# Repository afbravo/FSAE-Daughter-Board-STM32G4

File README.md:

# FSAE Daughter Board STM32G4
 Daughter Board KiCad Project for the NYU FSAE with a STM32G4 MCU.

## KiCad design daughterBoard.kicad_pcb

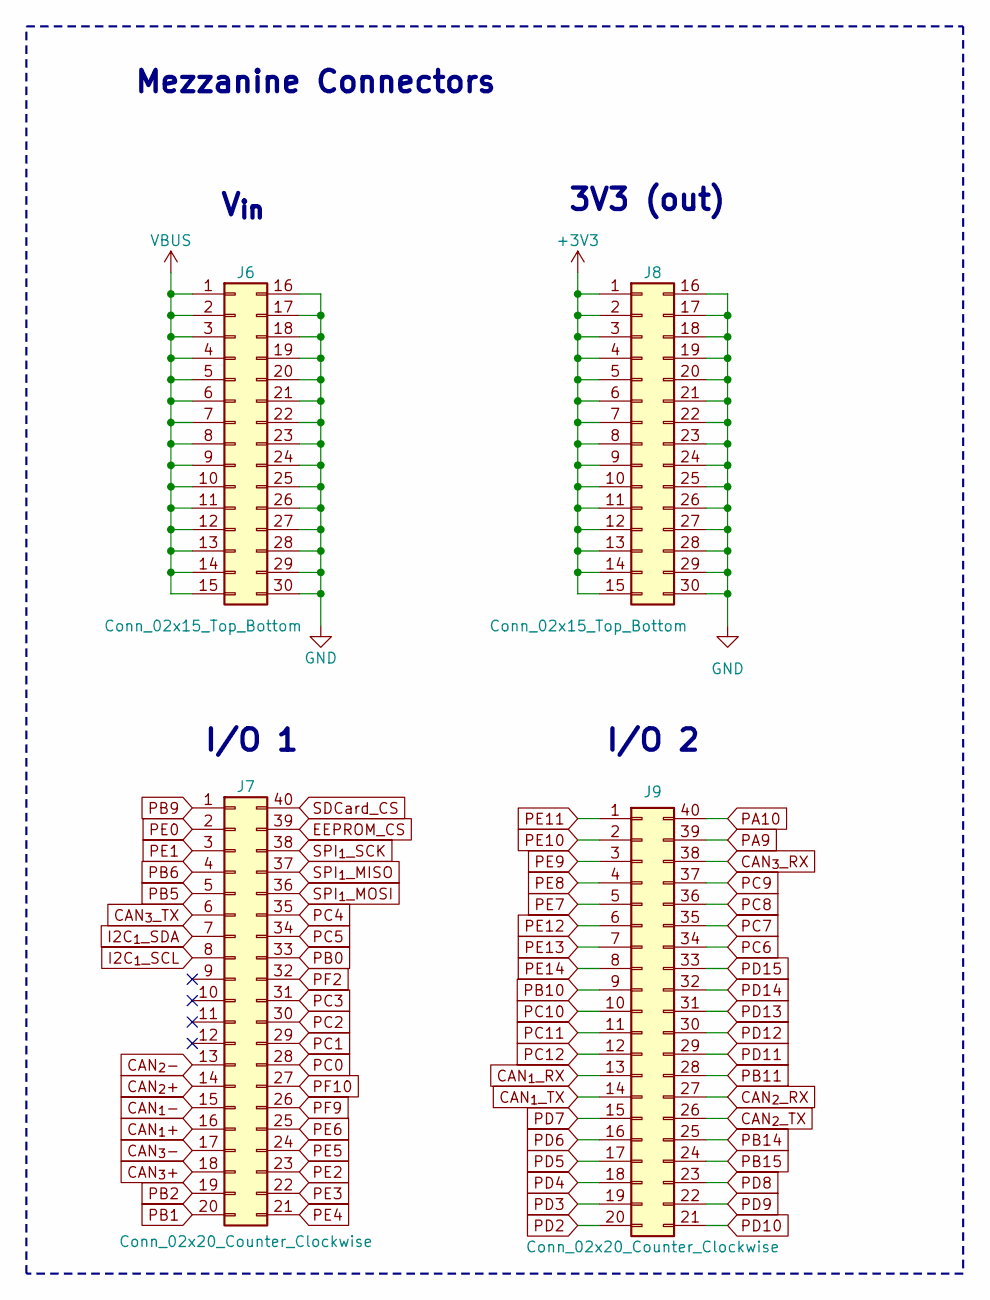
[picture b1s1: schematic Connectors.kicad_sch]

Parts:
J6, J8: Conn_02x15_Top_Bottom; DF40C-30DS; Digikey H11622CT-ND
J7, J9: Conn_02x20_Counter_Clockwise; DF40C-40DS; Digikey H11624CT-ND

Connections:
+3V3: J8.1, J8.2, J8.3, J8.4, J8.5, J8.6, J8.7, J8.8, J8.9, J8.10, J8.11, J8.12, J8.13, J8.14, J8.15; also elsewhere on the board
CAN_{1}+: J7.16; also elsewhere on the board
CAN_{1}-: J7.15; also elsewhere on the board
CAN_{1}_RX: J9.13; also elsewhere on the board
CAN_{1}_TX: J9.14; also elsewhere on the board
CAN_{2}+: J7.14; also elsewhere on the board
CAN_{2}-: J7.13; also elsewhere on the board
CAN_{2}_RX: J9.27; also elsewhere on the board
CAN_{2}_TX: J9.26; also elsewhere on the board
CAN_{3}+: J7.18; also elsewhere on the board
CAN_{3}-: J7.17; also elsewhere on the board
CAN_{3}_RX: J9.38; also elsewhere on the board
CAN_{3}_TX: J7.6; also elsewhere on the board
EEPROM_CS: J7.39; also elsewhere on the board
GND: J6.16, J6.17, J6.18, J6.19, J6.20, J6.21, J6.22, J6.23, J6.24, J6.25, J6.26, J6.27, J6.28, J6.29, J6.30, J8.16, J8.17, J8.18, J8.19, J8.20, J8.21, J8.22, J8.23, J8.24, J8.25, J8.26, J8.27, J8.28, J8.29, J8.30; also elsewhere on the board
I2C_{1}_SCL: J7.8; also elsewhere on the board
I2C_{1}_SDA: J7.7; also elsewhere on the board
PA9: J9.39; also elsewhere on the board
PA10: J9.40; also elsewhere on the board
PB0: J7.33; also elsewhere on the board
PB1: J7.20; also elsewhere on the board
PB2: J7.19; also elsewhere on the board
PB5: J7.5; also elsewhere on the board
PB6: J7.4; also elsewhere on the board
PB9: J7.1; also elsewhere on the board
PB10: J9.9; also elsewhere on the board
PB11: J9.28; also elsewhere on the board
PB14: J9.25; also elsewhere on the board
PB15: J9.24; also elsewhere on the board
PC0: J7.28; also elsewhere on the board
PC1: J7.29; also elsewhere on the board
PC2: J7.30; also elsewhere on the board
PC3: J7.31; also elsewhere on the board
PC4: J7.35; also elsewhere on the board
PC5: J7.34; also elsewhere on the board
PC6: J9.34; also elsewhere on the board
PC7: J9.35; also elsewhere on the board
PC8: J9.36; also elsewhere on the board
PC9: J9.37; also elsewhere on the board
PC10: J9.10; also elsewhere on the board
PC11: J9.11; also elsewhere on the board
PC12: J9.12; also elsewhere on the board
PD2: J9.20; also elsewhere on the board
PD3: J9.19; also elsewhere on the board
PD4: J9.18; also elsewhere on the board
PD5: J9.17; also elsewhere on the board
PD6: J9.16; also elsewhere on the board
PD7: J9.15; also elsewhere on the board
PD8: J9.23; also elsewhere on the board
PD9: J9.22; also elsewhere on the board
PD10: J9.21; also elsewhere on the board
PD11: J9.29; also elsewhere on the board
PD12: J9.30; also elsewhere on the board
PD13: J9.31; also elsewhere on the board
PD14: J9.32; also elsewhere on the board
PD15: J9.33; also elsewhere on the board
PE0: J7.2; also elsewhere on the board
PE1: J7.3; also elsewhere on the board
PE2: J7.23; also elsewhere on the board
PE3: J7.22; also elsewhere on the board
PE4: J7.21; also elsewhere on the board
PE5: J7.24; also elsewhere on the board
PE6: J7.25; also elsewhere on the board
PE7: J9.5; also elsewhere on the board
PE8: J9.4; also elsewhere on the board
PE9: J9.3; also elsewhere on the board
PE10: J9.2; also elsewhere on the board
PE11: J9.1; also elsewhere on the board
PE12: J9.6; also elsewhere on the board
PE13: J9.7; also elsewhere on the board
PE14: J9.8; also elsewhere on the board
PF2: J7.32; also elsewhere on the board
PF9: J7.26; also elsewhere on the board
PF10: J7.27; also elsewhere on the board
SDCard_CS: J7.40; also elsewhere on the board
SPI_{1}_MISO: J7.37; also elsewhere on the board
SPI_{1}_MOSI: J7.36; also elsewhere on the board
SPI_{1}_SCK: J7.38; also elsewhere on the board
VBUS: J6.1, J6.2, J6.3, J6.4, J6.5, J6.6, J6.7, J6.8, J6.9, J6.10, J6.11, J6.12, J6.13, J6.14, J6.15; also elsewhere on the board

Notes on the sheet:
I/O 1
Mezzanine Connectors
I/O 2
V_{in}
3V3 (out)

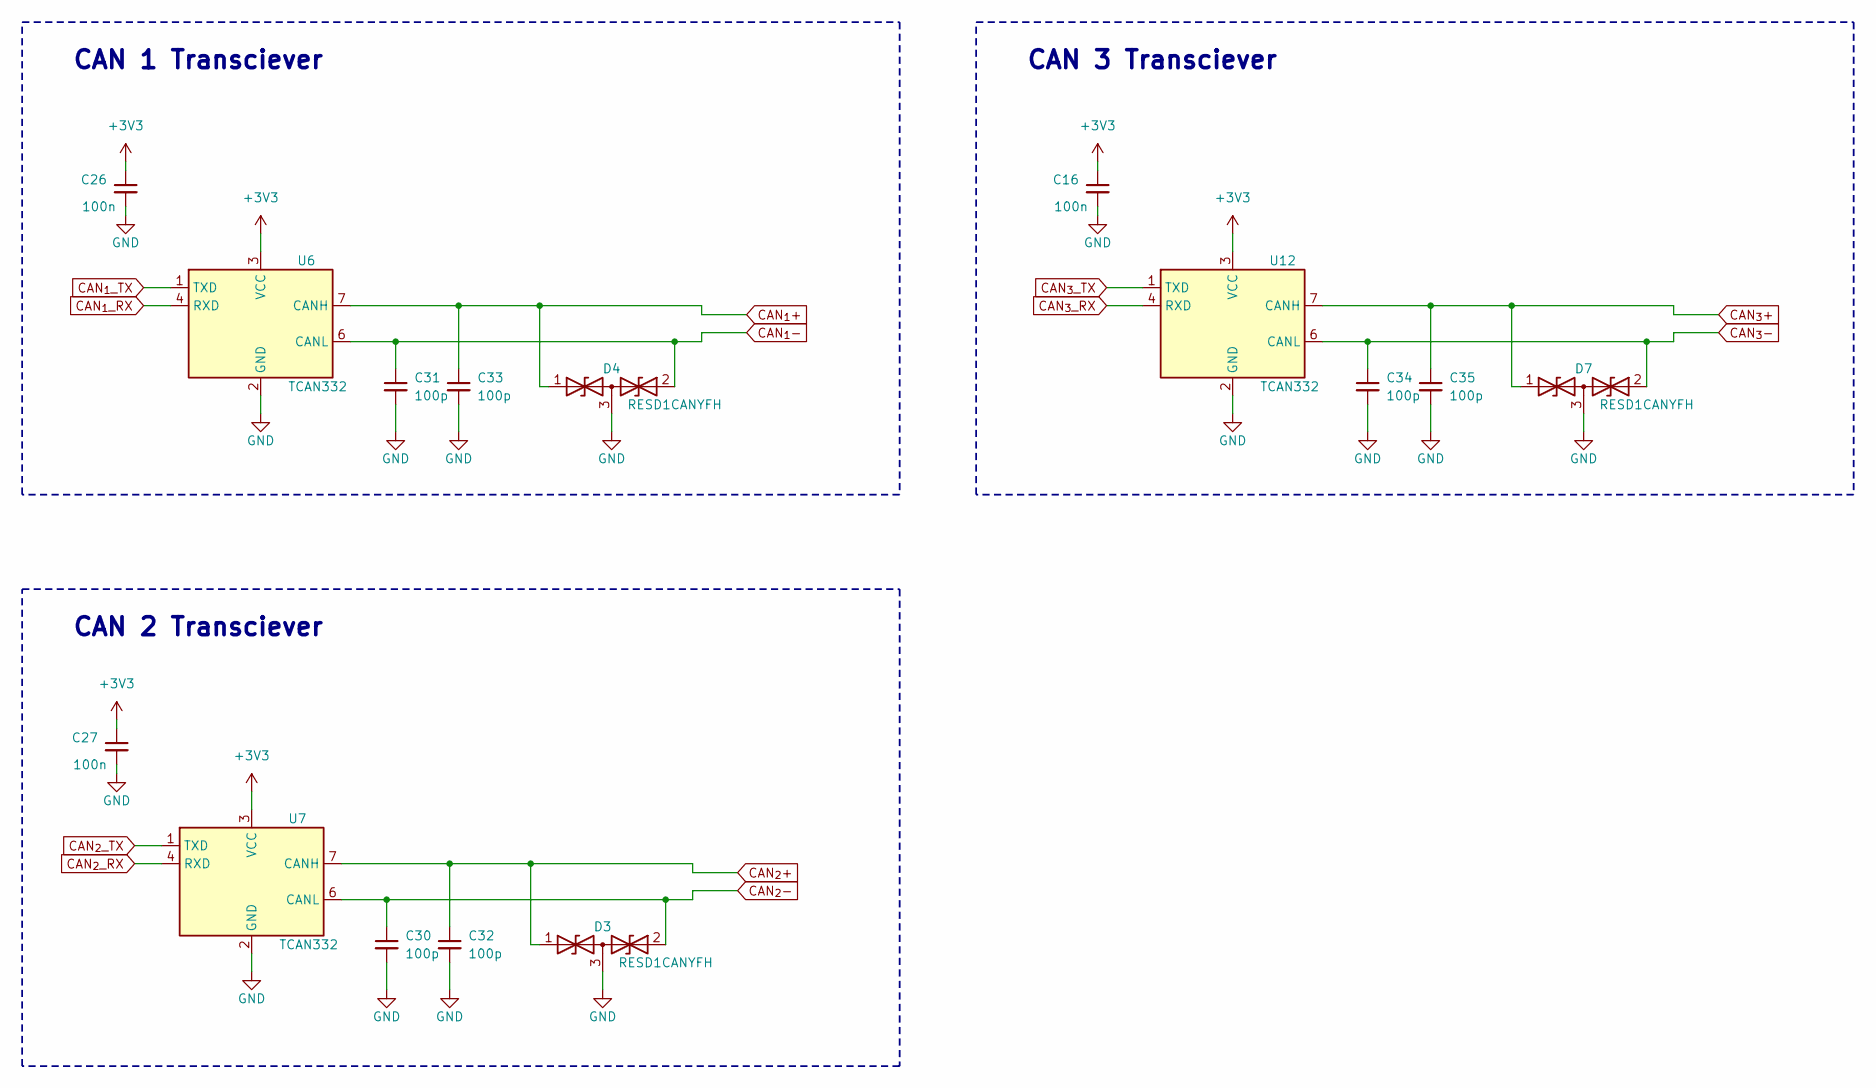
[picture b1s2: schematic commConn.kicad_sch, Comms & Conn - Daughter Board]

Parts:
C16, C26, C27: 100n; C_0201_0603Metric; Digikey 490-5405-1-ND
C30, C31, C32, C33, C34, C35: 100p; C_0402_1005Metric; Digikey 490-5922-1-ND
D3, D4, D7: RESD1CANYFH; SOT-323_SC-70; Digikey 846-RESD1CANYFHT116CT-ND
U6, U7, U12: TCAN332; SOIC-8_3.9x4.9mm_P1.27mm; Digikey 296-43711-1-ND

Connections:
+3V3: C16.1, C26.1, C27.1, U6.3 (VCC), U7.3 (VCC), U12.3 (VCC); also elsewhere on the board
CAN_{1}+: C33.1, D4.1 (A1), U6.7 (CANH); also elsewhere on the board
CAN_{1}-: C31.1, D4.2 (A2), U6.6 (CANL); also elsewhere on the board
CAN_{1}_RX: U6.4 (RXD); also elsewhere on the board
CAN_{1}_TX: U6.1 (TXD); also elsewhere on the board
CAN_{2}+: C32.1, D3.1 (A1), U7.7 (CANH); also elsewhere on the board
CAN_{2}-: C30.1, D3.2 (A2), U7.6 (CANL); also elsewhere on the board
CAN_{2}_RX: U7.4 (RXD); also elsewhere on the board
CAN_{2}_TX: U7.1 (TXD); also elsewhere on the board
CAN_{3}+: C35.1, D7.1 (A1), U12.7 (CANH); also elsewhere on the board
CAN_{3}-: C34.1, D7.2 (A2), U12.6 (CANL); also elsewhere on the board
CAN_{3}_RX: U12.4 (RXD); also elsewhere on the board
CAN_{3}_TX: U12.1 (TXD); also elsewhere on the board
GND: C16.2, C26.2, C27.2, C30.2, C31.2, C32.2, C33.2, C34.2, C35.2, D3.3 (common), D4.3 (common), D7.3 (common), U6.2 (GND), U7.2 (GND), U12.2 (GND); also elsewhere on the board

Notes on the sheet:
CAN 2 Transciever
CAN 3 Transciever
CAN 1 Transciever

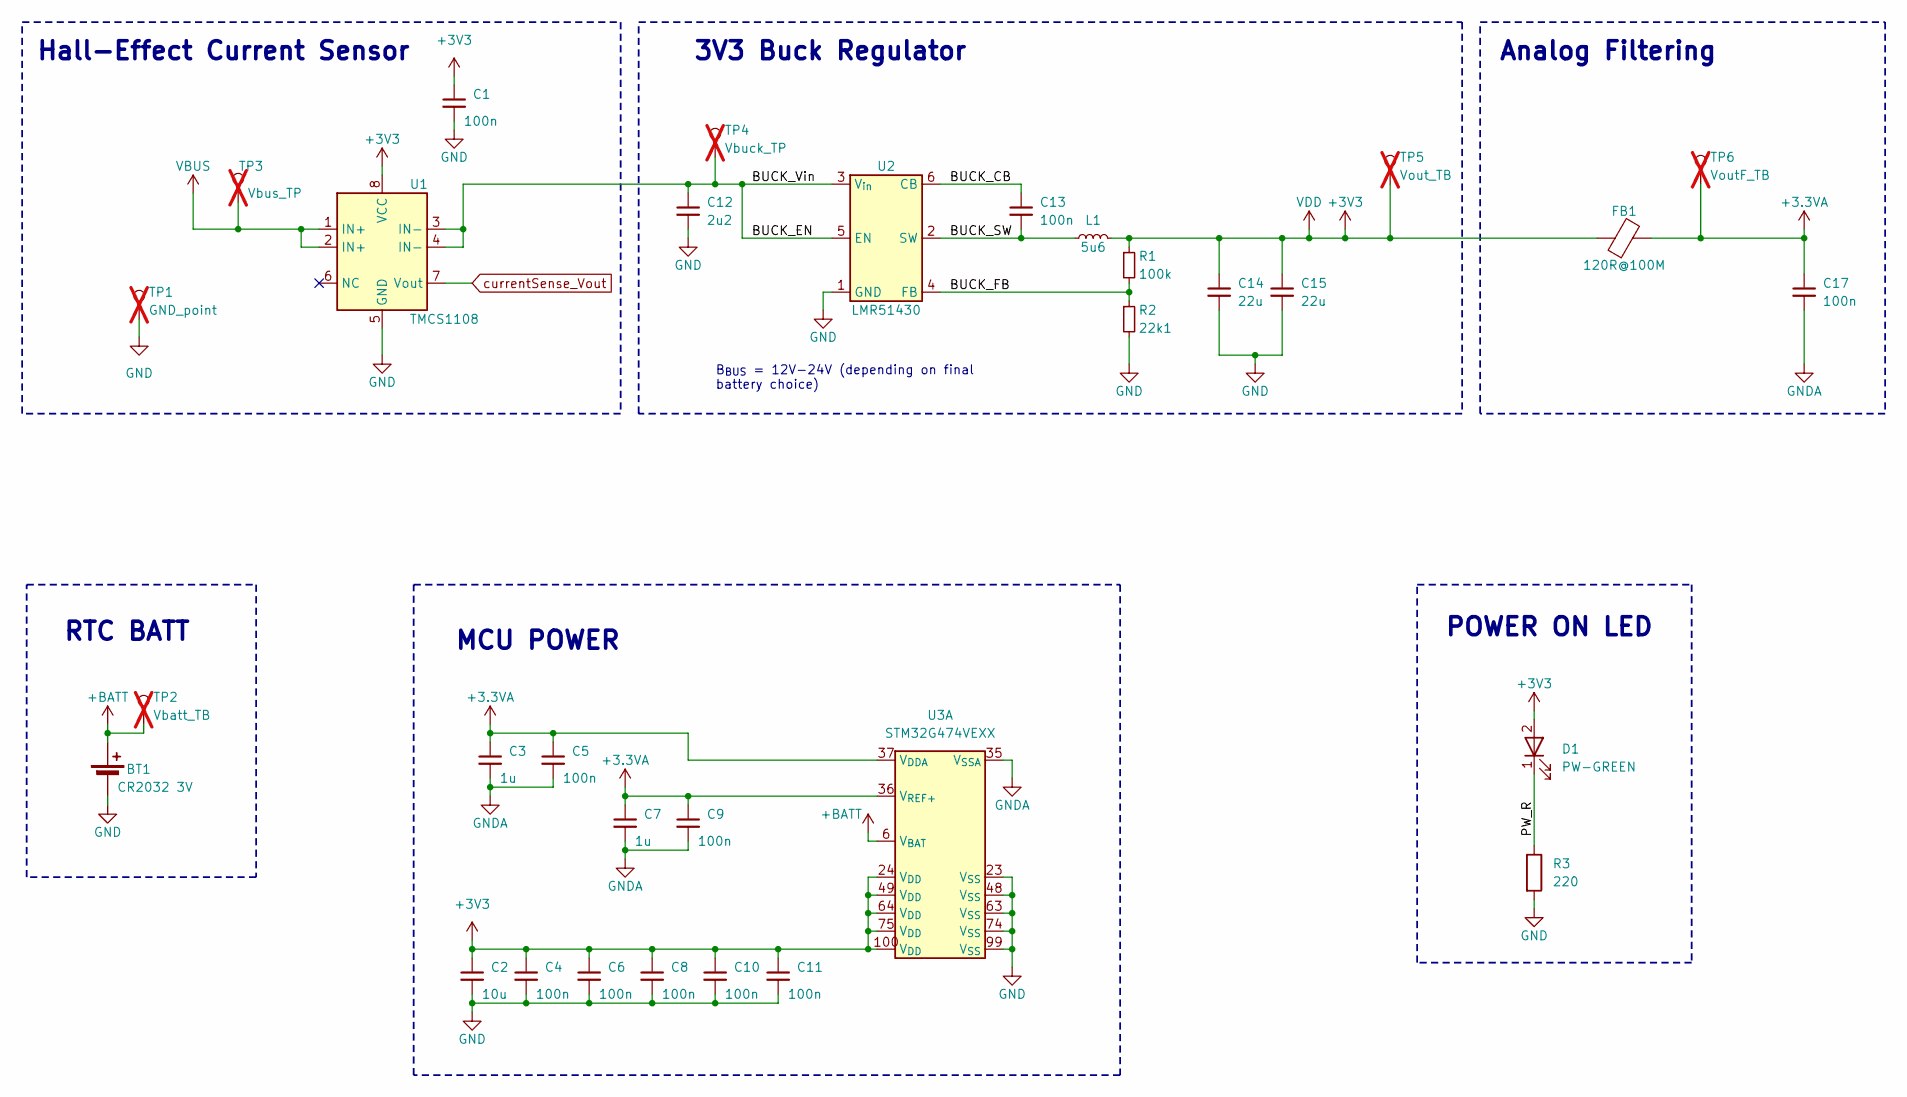
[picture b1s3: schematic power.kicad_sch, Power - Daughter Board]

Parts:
BT1: CR2032 3V; BU2032SM-HD-G; Digikey BU2032SM-HD-GCT-ND
C1, C4, C5, C6, C8, C9, C10, C11, C13, C17: 100n; C_0201_0603Metric; Digikey 490-5405-1-ND
C2: 10u; C_0402_1005Metric; Digikey 490-GRM155R60J106ME05DDKR-ND
C3, C7: 1u; C_0402_1005Metric; Digikey 490-13339-1-ND
C12: 2u2; C_0603_1608Metric; Digikey 587-2909-1-ND
C14, C15: 22u; C_0603_1608Metric; Digikey 1276-1274-1-ND
D1: PW-GREEN; LED_0603_1608Metric; Digikey 160-1446-1-ND
FB1: 120R@100M; R_0402_1005Metric; Digikey 490-1005-1-ND
L1: 5u6; ASPI-6045S; Digikey 535-ASPI-6045S-5R6M-TCT-ND
R1: 100k; R_0402_1005Metric; Digikey RMCF0402FT100KCT-ND
R2: 22k1; R_0603_1608Metric; Digikey P22.1KDBCT-ND
R3: 220; R_0402_1005Metric; Digikey 1292-WR04X2200FTLCT-ND
TP1: GND_point; TestPoint_Pad_4.0x4.0mm; not fitted
TP2: Vbatt_TB; TestPoint_Pad_D1.5mm; not fitted
TP3: Vbus_TP; TestPoint_Pad_D1.5mm; not fitted
TP4: Vbuck_TP; TestPoint_Pad_D1.5mm; not fitted
TP5: Vout_TB; TestPoint_Pad_D1.5mm; not fitted
TP6: VoutF_TB; TestPoint_Pad_D1.5mm; not fitted
U1: TMCS1108; SOIC-8_3.9x4.9mm_P1.27mm; Digikey 296-TMCS1108A3BQDRQ1CT-ND
U2: LMR51430; SOT-23-6; Digikey 296-LMR51430XFDDCRCT-ND
U3: STM32G474VEXX; LQFP-100_14x14mm_P0.5mm; Digikey 497-STM32G474VET3-ND

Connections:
+3.3VA: C3.1, C5.1, C7.1, C9.1, C17.1, FB1.2, TP6.1, U3.36 (V_{REF+}), U3.37 (V_{DDA})
+3V3: C1.1, C2.1, C4.1, C6.1, C8.1, C10.1, C11.1, C14.1, C15.1, D1.2 (A), FB1.1, L1.2, R1.1, TP5.1, U1.8 (VCC), U3.24 (V_{DD}), U3.49 (V_{DD}), U3.64 (V_{DD}), U3.75 (V_{DD}), U3.100 (V_{DD}); also elsewhere on the board
+BATT: BT1.1 (+), TP2.1, U3.6 (V_{BAT})
/Power/BUCK_CB: C13.1, U2.6 (CB)
/Power/BUCK_EN: C12.1, TP4.1, U1.3 (IN-), U1.4 (IN-), U2.3 (V_{in}), U2.5 (EN)
/Power/BUCK_FB: R1.2, R2.1, U2.4 (FB)
/Power/BUCK_SW: C13.2, L1.1, U2.2 (SW)
/Power/PW_R: D1.1 (K), R3.1
GND: BT1.2 (-), C1.2, C2.2, C4.2, C6.2, C8.2, C10.2, C11.2, C12.2, C14.2, C15.2, R2.2, R3.2, TP1.1, U1.5 (GND), U2.1 (GND), U3.23 (V_{SS}), U3.48 (V_{SS}), U3.63 (V_{SS}), U3.74 (V_{SS}), U3.99 (V_{SS}); also elsewhere on the board
GNDA: C3.2, C5.2, C7.2, C9.2, C17.2, U3.35 (V_{SSA})
VBUS: TP3.1, U1.1 (IN+), U1.2 (IN+); also elsewhere on the board
currentSense_Vout: U1.7 (Vout); also elsewhere on the board

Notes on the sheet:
3V3 Buck Regulator
RTC BATT
MCU POWER
Hall-Effect Current Sensor
Analog Filtering
POWER ON LED
B_{BUS} = 12V-24V (depending on final battery choice)

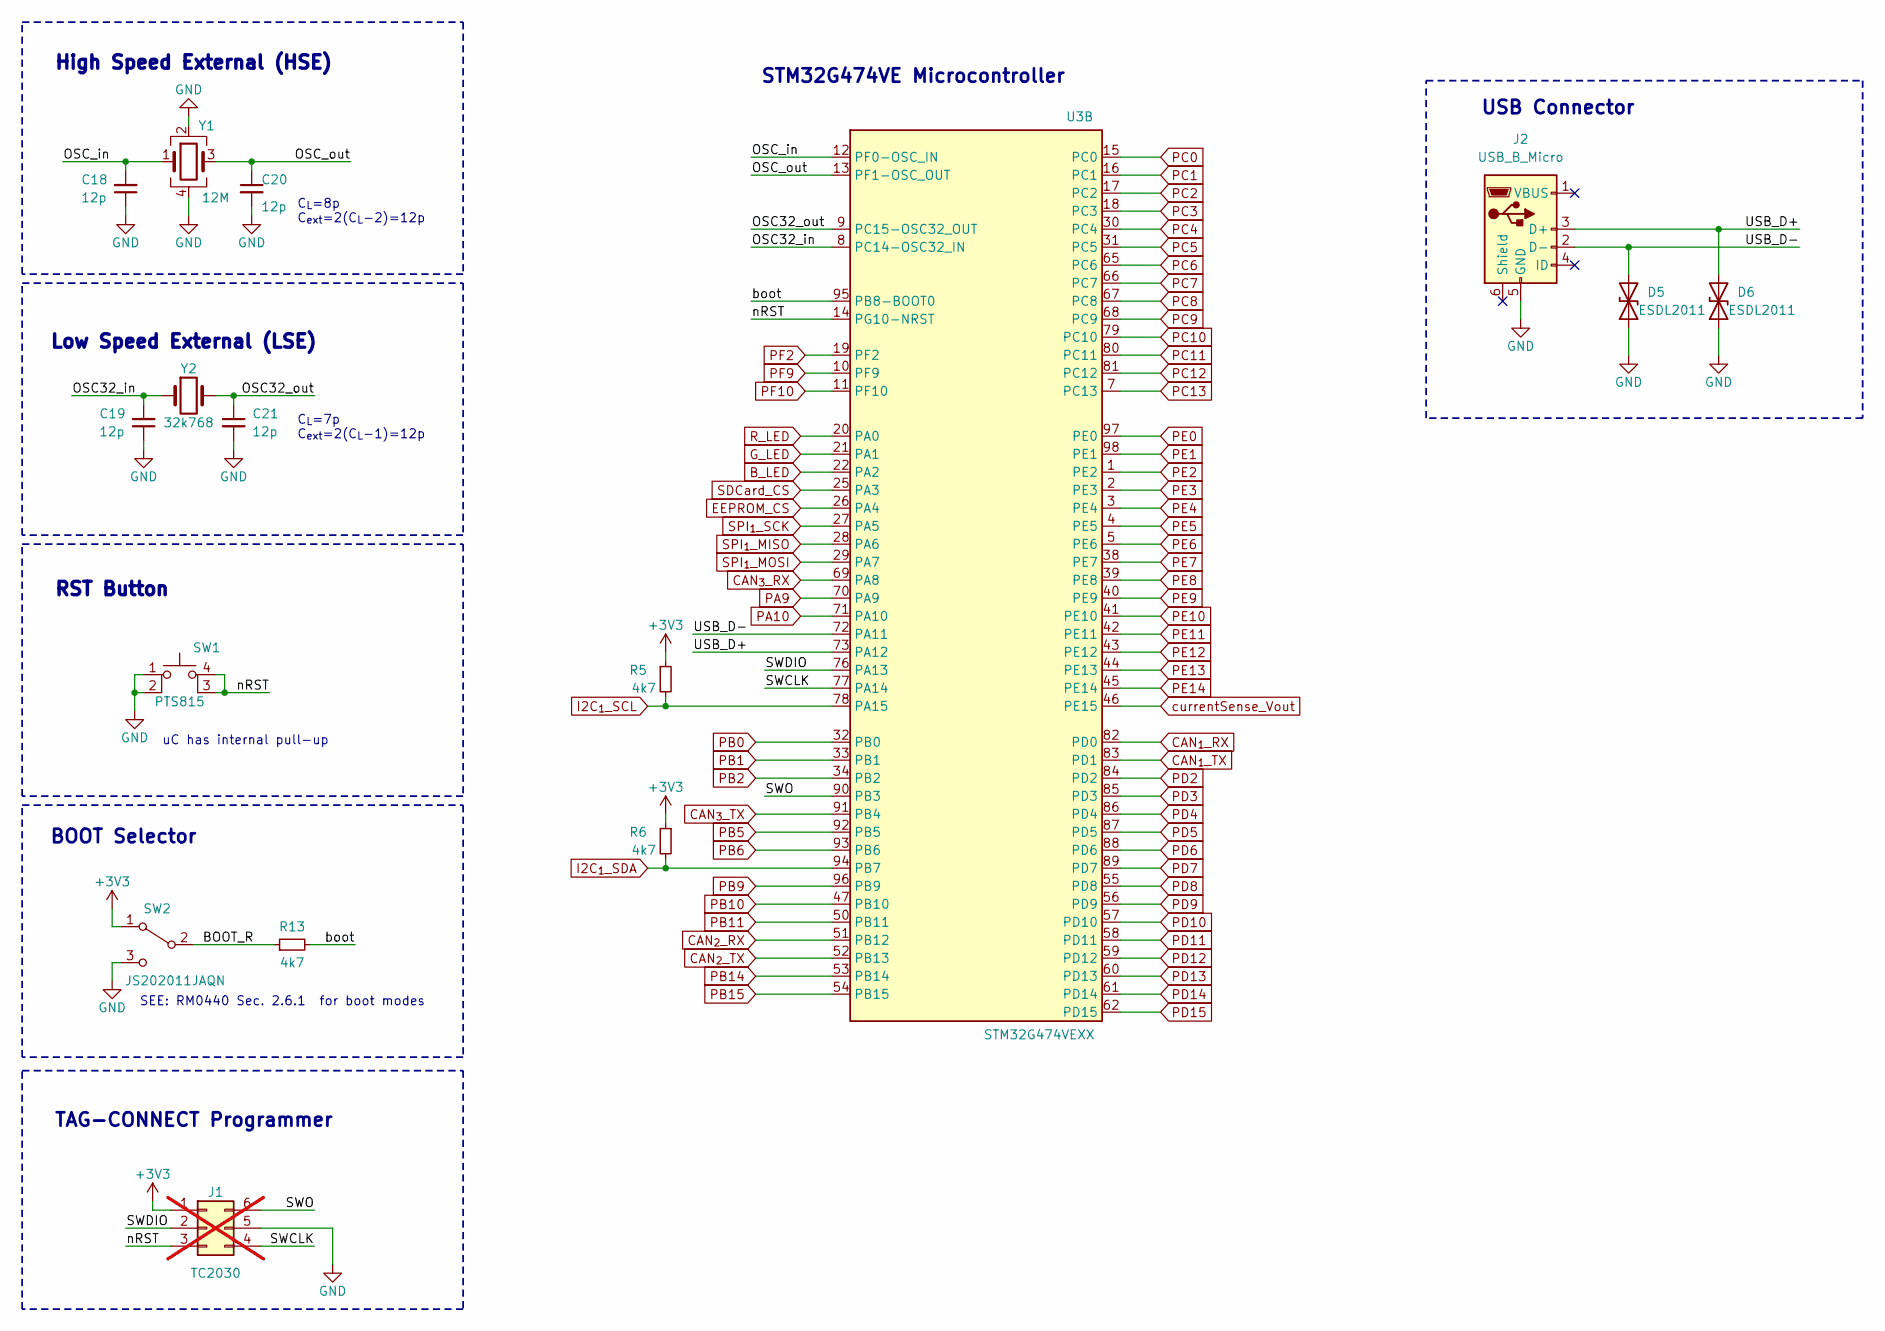
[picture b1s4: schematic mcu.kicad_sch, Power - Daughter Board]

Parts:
C18, C19, C20, C21: 12p; C_0402_1005Metric; Digikey 490-11190-1-ND
D5, D6: ESDL2011; D_0201_0603Metric; Digikey 488-ESDL2011PFCT5GCT-ND
J1: TC2030; Tag-Connect_TC2030-IDC-FP_2x03_P1.27mm_Vertical; Digikey N/A; not fitted
J2: USB_B_Micro; USB_Micro-B_Amphenol_10118193-0001LF_Horizontal; Digikey 609-4616-1-ND
R5, R6, R13: 4k7; R_0402_1005Metric; Digikey 311-4.7KLRCT-ND
SW1: PTS815; Digikey CKN12215-1-ND
SW2: JS202011JAQN; JS102011JAQN; Digikey CKN10722CT-ND
U3: STM32G474VEXX; LQFP-100_14x14mm_P0.5mm; Digikey 497-STM32G474VET3-ND
Y1: 12M; Crystal_SMD_2520-4Pin_2.5x2.0mm; Digikey 535-13520-1-ND
Y2: 32k768; Crystal_SMD_3215-2Pin_3.2x1.5mm; Digikey 728-1074-1-ND

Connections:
+3V3: J1.1, R5.1, R6.1, SW2.1 (A); also elsewhere on the board
/Microcontroller/BOOT_R: R13.1, SW2.2 (B)
/Microcontroller/OSC32_in: C19.2, U3.8 (PC14-OSC32_IN), Y2.1
/Microcontroller/OSC32_out: C21.1, U3.9 (PC15-OSC32_OUT), Y2.2
/Microcontroller/OSC_in: C18.2, U3.12 (PF0-OSC_IN), Y1.1
/Microcontroller/OSC_out: C20.1, U3.13 (PF1-OSC_OUT), Y1.3
/Microcontroller/SWCLK: J1.4, U3.77 (PA14)
/Microcontroller/SWDIO: J1.2, U3.76 (PA13)
/Microcontroller/SWO: J1.6, U3.90 (PB3)
/Microcontroller/USB_D+: D6.2 (A2), J2.3 (D+), U3.73 (PA12)
/Microcontroller/USB_D-: D5.2 (A2), J2.2 (D-), U3.72 (PA11)
/Microcontroller/boot: R13.2, U3.95 (PB8-BOOT0)
/Microcontroller/nRST: J1.3, SW1.3 (K), SW1.4 (A), U3.14 (PG10-NRST)
B_LED: U3.22 (PA2); also elsewhere on the board
CAN_{1}_RX: U3.82 (PD0); also elsewhere on the board
CAN_{1}_TX: U3.83 (PD1); also elsewhere on the board
CAN_{2}_RX: U3.51 (PB12); also elsewhere on the board
CAN_{2}_TX: U3.52 (PB13); also elsewhere on the board
CAN_{3}_RX: U3.69 (PA8); also elsewhere on the board
CAN_{3}_TX: U3.91 (PB4); also elsewhere on the board
EEPROM_CS: U3.26 (PA4); also elsewhere on the board
GND: C18.1, C19.1, C20.2, C21.2, D5.1 (A1), D6.1 (A1), J1.5, J2.5 (GND), SW1.1, SW1.2, SW2.3 (C), Y1.2, Y1.4; also elsewhere on the board
G_LED: U3.21 (PA1); also elsewhere on the board
I2C_{1}_SCL: R5.2, U3.78 (PA15); also elsewhere on the board
I2C_{1}_SDA: R6.2, U3.94 (PB7); also elsewhere on the board
PA9: U3.70 (PA9); also elsewhere on the board
PA10: U3.71 (PA10); also elsewhere on the board
PB0: U3.32 (PB0); also elsewhere on the board
PB1: U3.33 (PB1); also elsewhere on the board
PB2: U3.34 (PB2); also elsewhere on the board
PB5: U3.92 (PB5); also elsewhere on the board
PB6: U3.93 (PB6); also elsewhere on the board
PB9: U3.96 (PB9); also elsewhere on the board
PB10: U3.47 (PB10); also elsewhere on the board
PB11: U3.50 (PB11); also elsewhere on the board
PB14: U3.53 (PB14); also elsewhere on the board
PB15: U3.54 (PB15); also elsewhere on the board
PC0: U3.15 (PC0); also elsewhere on the board
PC1: U3.16 (PC1); also elsewhere on the board
PC2: U3.17 (PC2); also elsewhere on the board
PC3: U3.18 (PC3); also elsewhere on the board
PC4: U3.30 (PC4); also elsewhere on the board
PC5: U3.31 (PC5); also elsewhere on the board
PC6: U3.65 (PC6); also elsewhere on the board
PC7: U3.66 (PC7); also elsewhere on the board
PC8: U3.67 (PC8); also elsewhere on the board
PC9: U3.68 (PC9); also elsewhere on the board
PC10: U3.79 (PC10); also elsewhere on the board
PC11: U3.80 (PC11); also elsewhere on the board
PC12: U3.81 (PC12); also elsewhere on the board
PC13: U3.7 (PC13)
PD2: U3.84 (PD2); also elsewhere on the board
PD3: U3.85 (PD3); also elsewhere on the board
PD4: U3.86 (PD4); also elsewhere on the board
PD5: U3.87 (PD5); also elsewhere on the board
PD6: U3.88 (PD6); also elsewhere on the board
PD7: U3.89 (PD7); also elsewhere on the board
PD8: U3.55 (PD8); also elsewhere on the board
PD9: U3.56 (PD9); also elsewhere on the board
PD10: U3.57 (PD10); also elsewhere on the board
PD11: U3.58 (PD11); also elsewhere on the board
PD12: U3.59 (PD12); also elsewhere on the board
PD13: U3.60 (PD13); also elsewhere on the board
PD14: U3.61 (PD14); also elsewhere on the board
PD15: U3.62 (PD15); also elsewhere on the board
PE0: U3.97 (PE0); also elsewhere on the board
PE1: U3.98 (PE1); also elsewhere on the board
PE2: U3.1 (PE2); also elsewhere on the board
PE3: U3.2 (PE3); also elsewhere on the board
PE4: U3.3 (PE4); also elsewhere on the board
PE5: U3.4 (PE5); also elsewhere on the board
PE6: U3.5 (PE6); also elsewhere on the board
PE7: U3.38 (PE7); also elsewhere on the board
PE8: U3.39 (PE8); also elsewhere on the board
PE9: U3.40 (PE9); also elsewhere on the board
PE10: U3.41 (PE10); also elsewhere on the board
PE11: U3.42 (PE11); also elsewhere on the board
PE12: U3.43 (PE12); also elsewhere on the board
PE13: U3.44 (PE13); also elsewhere on the board
PE14: U3.45 (PE14); also elsewhere on the board
PF2: U3.19 (PF2); also elsewhere on the board
PF9: U3.10 (PF9); also elsewhere on the board
PF10: U3.11 (PF10); also elsewhere on the board
R_LED: U3.20 (PA0); also elsewhere on the board
SDCard_CS: U3.25 (PA3); also elsewhere on the board
SPI_{1}_MISO: U3.28 (PA6); also elsewhere on the board
SPI_{1}_MOSI: U3.29 (PA7); also elsewhere on the board
SPI_{1}_SCK: U3.27 (PA5); also elsewhere on the board
currentSense_Vout: U3.46 (PE15); also elsewhere on the board

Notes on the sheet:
TAG-CONNECT Programmer
High Speed External (HSE)
Low Speed External (LSE)
C_{L}=8p C_{ext}=2(C_{L}-2)=12p
uC has internal pull-up
BOOT Selector
USB Connector
SEE: RM0440 Sec. 2.6.1 for boot modes
C_{L}=7p C_{ext}=2(C_{L}-1)=12p
RST Button
STM32G474VE Microcontroller

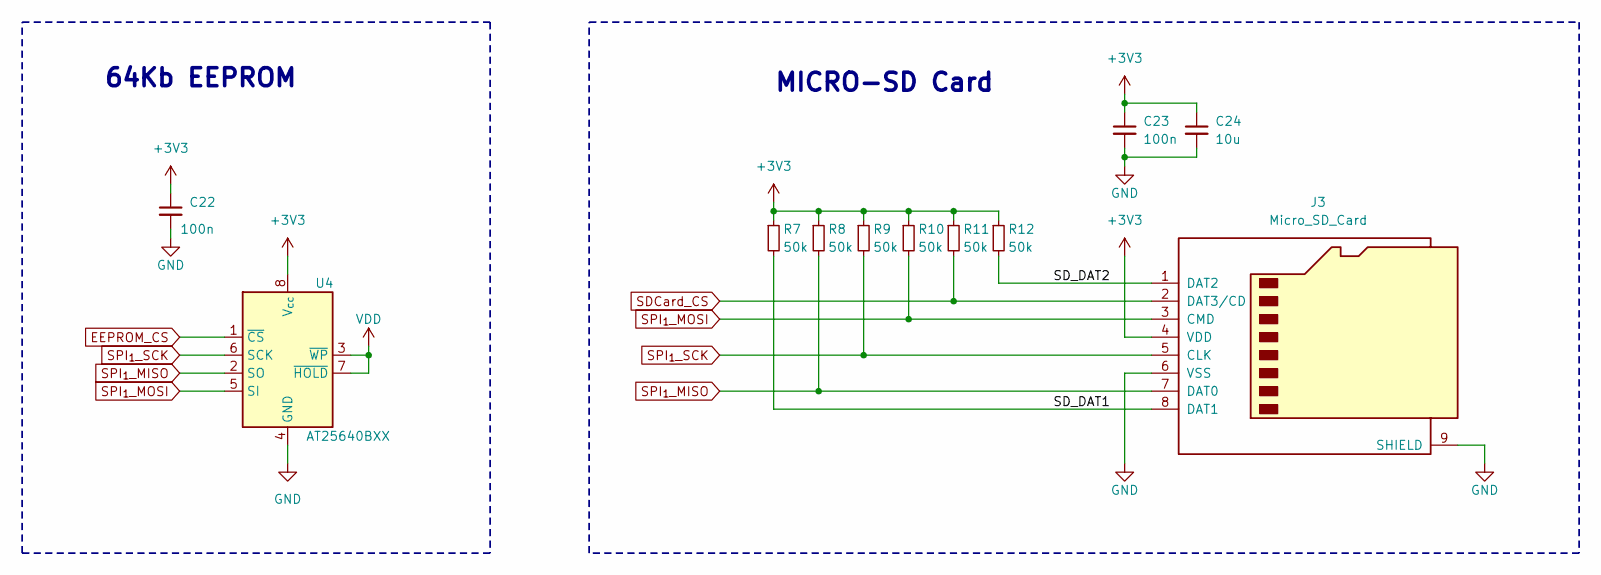
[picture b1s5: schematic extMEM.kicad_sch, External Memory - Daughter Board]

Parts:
C22, C23: 100n; C_0201_0603Metric; Digikey 490-5405-1-ND
C24: 10u; C_0402_1005Metric; Digikey 490-GRM155R60J106ME05DDKR-ND
J3: Micro_SD_Card; GCT_MEM2075-00-140-01-A; Digikey 2073-MEM2075-00-140-01-ADKR-ND
R7, R8, R9, R10, R11, R12: 50k; R_0603_1608Metric; Digikey 13-RT0603BRD0750KLCT-ND
U4: AT25640BXX; TSSOP-8_4.4x3mm_P0.65mm; Digikey AT25640B-XHL-TCT-ND

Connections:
+3V3: C22.1, C23.1, C24.1, J3.4 (VDD), R7.1, R8.1, R9.1, R10.1, R11.1, R12.1, U4.3 (~WP), U4.7 (~HOLD), U4.8 (V_{cc}); also elsewhere on the board
/External Memory/SD_DAT1: J3.8 (DAT1), R7.2
/External Memory/SD_DAT2: J3.1 (DAT2), R12.2
EEPROM_CS: U4.1 (~CS); also elsewhere on the board
GND: C22.2, C23.2, C24.2, J3.6 (VSS), J3.9 (SHIELD), U4.4 (GND); also elsewhere on the board
SDCard_CS: J3.2 (DAT3/CD), R11.2; also elsewhere on the board
SPI_{1}_MISO: J3.7 (DAT0), R8.2, U4.2 (SO); also elsewhere on the board
SPI_{1}_MOSI: J3.3 (CMD), R10.2, U4.5 (SI); also elsewhere on the board
SPI_{1}_SCK: J3.5 (CLK), R9.2, U4.6 (SCK); also elsewhere on the board

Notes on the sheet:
MICRO-SD Card
64Kb EEPROM

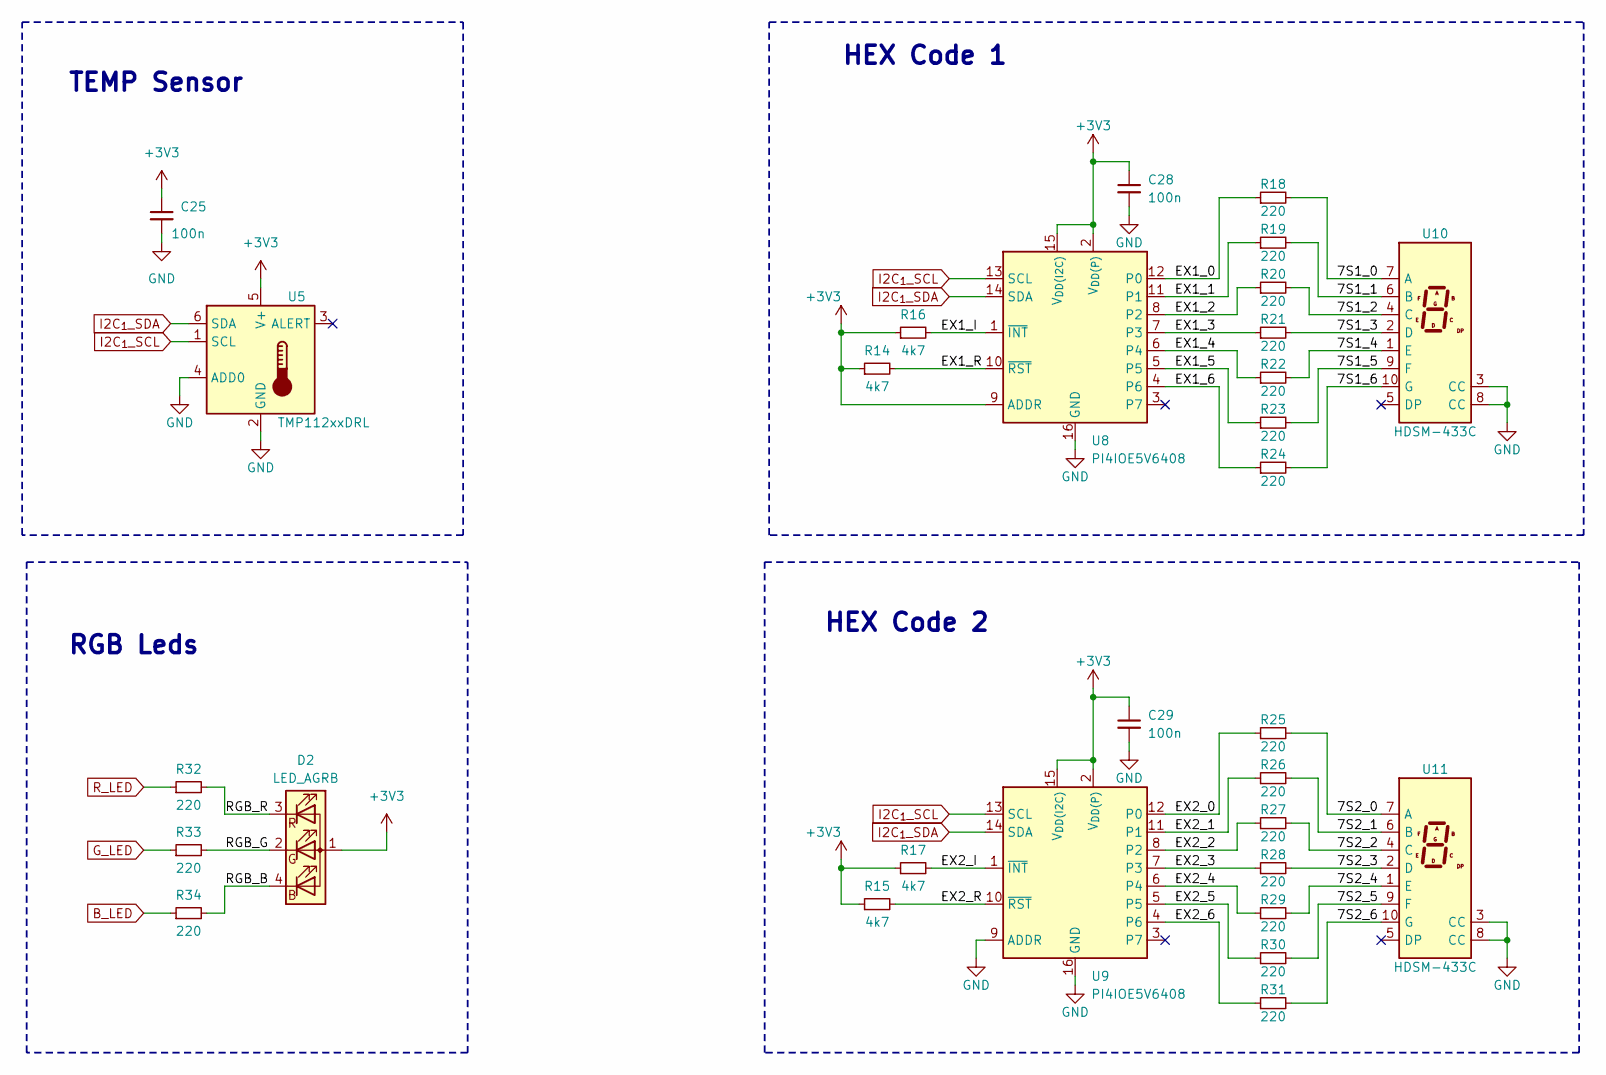
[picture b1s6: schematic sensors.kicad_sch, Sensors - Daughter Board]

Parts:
C25, C28, C29: 100n; C_0201_0603Metric; Digikey 490-5405-1-ND
D2: LED_AGRB; LED_ASMB-KTF0-0A306; Digikey 516-3906-1-ND
R14, R15, R16, R17: 4k7; R_0402_1005Metric; Digikey 311-4.7KLRCT-ND
R18, R19, R20, R21, R22, R23, R24, R25, R26, R27, R28, R29, R30, R31, R32, R33, R34: 220; R_0402_1005Metric; Digikey 1292-WR04X2200FTLCT-ND
U5: TMP112xxDRL; SOT-563; Digikey 296-38578-1-ND
U8, U9: PI4IOE5V6408; UQFN-16_1.8x2.6mm; Digikey PI4IOE5V6408ZTAEXDICT-ND
U10, U11: HDSM-433C; HDSM-431X_432X; Digikey 516-3498-1-ND

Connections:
+3V3: C25.1, C28.1, C29.1, D2.1 (A), R14.1, R15.1, R16.1, R17.1, U5.5 (V+), U8.2 (V_{DD(P)}), U8.9 (ADDR), U8.15 (V_{DD(I2C)}), U9.2 (V_{DD(P)}), U9.15 (V_{DD(I2C)}); also elsewhere on the board
/Sensors/7S1_0: R18.2, U10.7 (A)
/Sensors/7S1_1: R19.2, U10.6 (B)
/Sensors/7S1_2: R20.2, U10.4 (C)
/Sensors/7S1_3: R21.2, U10.2 (D)
/Sensors/7S1_4: R22.2, U10.1 (E)
/Sensors/7S1_5: R23.2, U10.9 (F)
/Sensors/7S1_6: R24.2, U10.10 (G)
/Sensors/7S2_0: R25.2, U11.7 (A)
/Sensors/7S2_1: R26.2, U11.6 (B)
/Sensors/7S2_2: R27.2, U11.4 (C)
/Sensors/7S2_3: R28.2, U11.2 (D)
/Sensors/7S2_4: R29.2, U11.1 (E)
/Sensors/7S2_5: R30.2, U11.9 (F)
/Sensors/7S2_6: R31.2, U11.10 (G)
/Sensors/EX1_0: R18.1, U8.12 (P0)
/Sensors/EX1_1: R19.1, U8.11 (P1)
/Sensors/EX1_2: R20.1, U8.8 (P2)
/Sensors/EX1_3: R21.1, U8.7 (P3)
/Sensors/EX1_4: R22.1, U8.6 (P4)
/Sensors/EX1_5: R23.1, U8.5
/Sensors/EX1_6: R24.1, U8.4 (P6)
/Sensors/EX1_I: R16.2, U8.1 (~INT)
/Sensors/EX1_R: R14.2, U8.10 (~RST)
/Sensors/EX2_0: R25.1, U9.12 (P0)
/Sensors/EX2_1: R26.1, U9.11 (P1)
/Sensors/EX2_2: R27.1, U9.8 (P2)
/Sensors/EX2_3: R28.1, U9.7 (P3)
/Sensors/EX2_4: R29.1, U9.6 (P4)
/Sensors/EX2_5: R30.1, U9.5
/Sensors/EX2_6: R31.1, U9.4 (P6)
/Sensors/EX2_I: R17.2, U9.1 (~INT)
/Sensors/EX2_R: R15.2, U9.10 (~RST)
/Sensors/RGB_B: D2.4 (BK), R34.2
/Sensors/RGB_G: D2.2 (GK), R33.2
/Sensors/RGB_R: D2.3 (RK), R32.2
B_LED: R34.1; also elsewhere on the board
GND: C25.2, C28.2, C29.2, U5.2 (GND), U5.4 (ADD0), U8.16 (GND), U9.9 (ADDR), U9.16 (GND), U10.3 (CC), U10.8 (CC), U11.3 (CC), U11.8 (CC); also elsewhere on the board
G_LED: R33.1; also elsewhere on the board
I2C_{1}_SCL: U5.1 (SCL), U8.13 (SCL), U9.13 (SCL); also elsewhere on the board
I2C_{1}_SDA: U5.6 (SDA), U8.14 (SDA), U9.14 (SDA); also elsewhere on the board
R_LED: R32.1; also elsewhere on the board

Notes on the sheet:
HEX Code 2
HEX Code 1
RGB Leds
TEMP Sensor

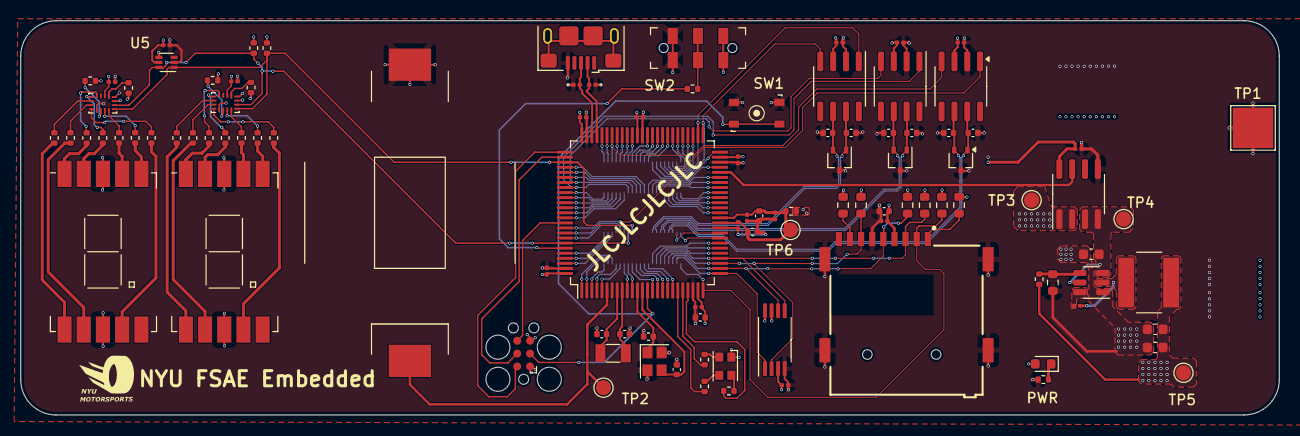
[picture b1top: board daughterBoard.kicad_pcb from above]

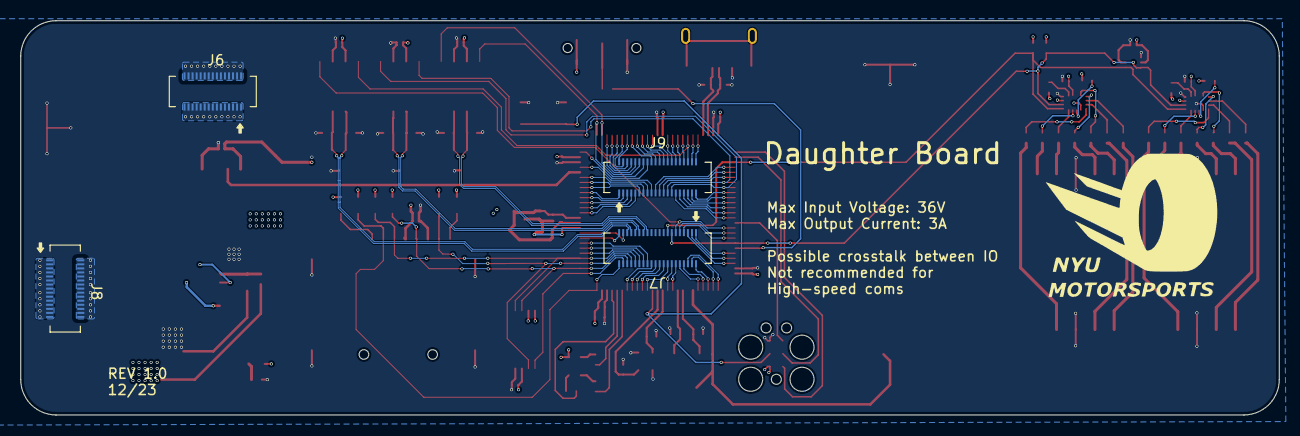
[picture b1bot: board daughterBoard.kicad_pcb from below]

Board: 4 copper layers, 124.5 x 39.0 mm, 107 parts (4 on the bottom side), 140 nets.
